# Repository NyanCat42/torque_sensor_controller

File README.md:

# Torque Sensor Controller for VESC E-Bike Assist

This repository contains hardware and firmware for an ESP32-S3 based torque sensor controller that talks to a [VESC](https://github.com/vedderb/bldc) over CAN bus.

The controller reads bottom bracket torque and cadence, computes an assist current target, and sends motor current commands to the VESC. It also tracks odometer data with FRAM-backed persistence and exposes a local web UI for status, tuning, and OTA firmware updates.

## Features

- Torque and cadence based pedal-assist control loop (10 ms period).
- CAN communication to VESC at 500 kbit/s.
- Odometer and speed tracking with persistent FRAM storage.
- Wi-Fi station mode with fallback access point mode.
- Embedded HTTP console for telemetry, runtime config, and calibration.
- OTA firmware upload endpoint.
- TCP bridge for VESC tool connectivity over Wi-Fi.

## Repository Layout

- `lauryno_torque_controller_hardware/`: KiCad schematic, PCB, and BOM.
- `lauryno_torque_controller_software/`: PlatformIO firmware project.
- `documents/`: reference documents, including [torque sensor datasheet](./documents/S135daff485444e569ac136541eaddd83u.pdf).
- `images/`: board render and finished board photo.

## Hardware

Hardware highlights:

- ESP32-S3 module as main controller.
- CAN transceiver interface to VESC.
- FRAM storage for high-endurance persistent data.
- 2 MOSFET outputs and a buck stage for front/rear LED lighting.

The PCB was designed to fit AISLER simple 2-layer constraints for low-cost fabrication.

Available hardware design artifacts:

- Schematic: [lauryno_torque_controller.kicad_sch](./lauryno_torque_controller_hardware/lauryno_torque_controller.kicad_sch)
- PCB layout: [lauryno_torque_controller.kicad_pcb](./lauryno_torque_controller_hardware/lauryno_torque_controller.kicad_pcb)
- BOM: [lauryno_torque_controller.csv](./lauryno_torque_controller_hardware/lauryno_torque_controller.csv)

## Firmware Architecture

Main runtime modules:

- `PedalAssistManager`: torque/cadence processing and motor current command generation.
- `VescCan`: CAN transport and VESC status/current command handling.
- `OdometerManager`: wheel pulse tracking, speed estimation, and persistence.
- `FramStorage`: I2C FRAM read/write backend.
- `NetworkManager`: station connect with timeout and fallback AP startup.
- `OtaHttpServer`: web UI, REST endpoints, and OTA upload flow.
- `VescTcpBridge`: optional TCP bridge (disabled by default).

Task model:

- Pedal-assist control task on core 1.
- Communication task (HTTP + TCP bridge update loop) on core 0.
- Main loop polls CAN and updates odometer processing.

## Quick Start

First flash has to be done over UART, later ones can be done OTA.

1. Install PlatformIO CLI.
2. Open terminal in `lauryno_torque_controller_software/`.
3. Create a local `platformio.secrets.ini` (this file is git-ignored):

```ini
[env:esp32-s3-devkitc-1]
build_flags =
	-DWIFI_STA_SSID=\"YOUR_WIFI_SSID\"
	-DWIFI_STA_PASSWORD=\"YOUR_WIFI_PASSWORD\"
```

4. Build firmware:

```bash
pio run -e esp32-s3-devkitc-1
```

5. Upload over UART (pads at top left of board):

```bash
pio run -e esp32-s3-devkitc-1 -t upload
```

## First Boot Notes

- Device tries configured Wi-Fi STA first, then falls back to AP mode if connection times out.
- AP SSID format: `TorqueCtrl-Setup-<chipid>`.
- mDNS host: `lauryno-dviratis.local`.
- HTTP console runs on port `80`.
- VESC TCP bridge port: `65102` (can be toggled from API/UI).
- **Run pedal sensor zero calibration** after installation using `POST /api/pedal/calibrate_zero`.

## OTA Update

Firmware can be uploaded from the web UI or directly by HTTP multipart upload:

```bash
curl -F "file=@.pio/build/esp32-s3-devkitc-1/firmware.bin" http://lauryno-dviratis.local/api/update
```

After a successful upload, the controller restarts automatically.

## Configuration Baseline

Hardware pins:

- CAN: TX GPIO 15, RX GPIO 7, 500000 bit/s.
- Odometer hall input: GPIO 9.
- FRAM I2C: SDA GPIO 6, SCL GPIO 5, base address `0x50`.
- Torque ADC input: GPIO 1.
- Cadence input: GPIO 2.

VESC IDs: 

- Local controller `42`, target controller `69` (make sure this matches the CAN ID of your VESC).

See `lauryno_torque_controller_software/include/app_config.h` for the full set of constants and limits.

## Open-Source License

This project is licensed under **CERN Open Hardware Licence Version 2 - Permissive** (`CERN-OHL-P-2.0`).

See the repository [LICENSE](./LICENSE) file for the project license notice and the official CERN-OHL-P v2 text reference.

## References

- VESC firmware project: [https://github.com/vedderb/bldc](https://github.com/vedderb/bldc)
- Torque sensor reference document: [S135daff485444e569ac136541eaddd83u.pdf](./documents/S135daff485444e569ac136541eaddd83u.pdf)

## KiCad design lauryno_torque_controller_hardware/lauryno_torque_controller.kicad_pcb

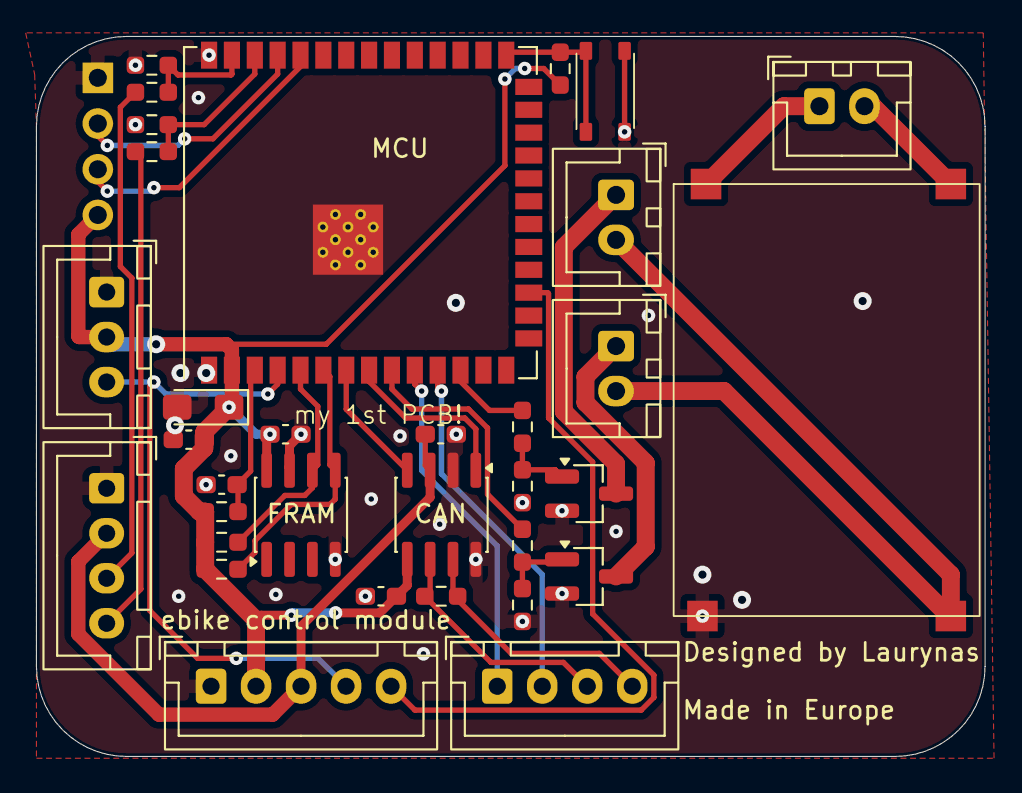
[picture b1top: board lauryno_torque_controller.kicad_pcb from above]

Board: 2 copper layers, 52.7 x 40.0 mm, 34 parts (0 on the bottom side), 27 nets.

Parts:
Battery1: Conn_01x02_Socket; JST_XH_B2B-XH-A_1x02_P2.50mm_Vertical
Boot1: SW_Push; SW_Push_SPST_NO_Alps_SKRK
C2, C4, C5, C6: 0.1u; C_0603_1608Metric_Pad1.08x0.95mm_HandSolder
C3: 1u; C_0603_1608Metric_Pad1.08x0.95mm_HandSolder
C7: 22u; CP_EIA-3216-18_Kemet-A_HandSolder
CAN_chip1: TJA1051T-3; SOIC-8_3.9x4.9mm_P1.27mm
Chineesium_60V_to_12V1: Conn_01x04_Pin; PinHeader_1x04_P2.54mm_Vertical
ESP32: ESP32-S3-WROOM-1; ESP32-S3-WROOM-1U
FRAM1: FM24CL16B; SOIC-8_3.9x4.9mm_P1.27mm
Flashing_UART1: Conn_01x04_Socket; PinHeader_1x04_P2.54mm_Vertical
LED1, LED2: Conn_01x02_Socket; JST_XH_B2B-XH-A_1x02_P2.50mm_Vertical
Q1, Q2: IRLML2502TRPBF; SOT-23_Handsoldering
R1, R4, R7, R8, R9, R12: 10k; R_0603_1608Metric_Pad0.98x0.95mm_HandSolder
R2: 120; R_0603_1608Metric_Pad0.98x0.95mm_HandSolder
R5, R6: 220; R_0603_1608Metric_Pad0.98x0.95mm_HandSolder
R10, R11: 15k; R_0603_1608Metric_Pad0.98x0.95mm_HandSolder
R13, R14: 4.7k; R_0603_1608Metric_Pad0.98x0.95mm_HandSolder
Throttle1: Conn_01x03_Socket; JST_XH_B3B-XH-A_1x03_P2.50mm_Vertical
Torque_sensor1: Conn_01x04_Socket; JST_XH_B4B-XH-A_1x04_P2.50mm_Vertical
VESC1: Conn_01x05_Socket; JST_XH_B5B-XH-A_1x05_P2.50mm_Vertical
VESC_coms1: Conn_01x04_Socket; JST_XH_B4B-XH-A_1x04_P2.50mm_Vertical

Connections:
/3V3: C2.1, C4.1, C6.1, C7.1, CAN_chip1.5 (VIO), ESP32.2 (3V3), FRAM1.8 (VDD), Flashing_UART1.4, R1.1, R4.1, R13.1, R14.1, Throttle1.2, VESC1.2
/5V: C5.1, CAN_chip1.3 (VCC), Torque_sensor1.2, VESC1.3
/CAN_RX: CAN_chip1.1 (TXD), ESP32.8 (IO15)
/CAN_TX: CAN_chip1.4 (RXD), ESP32.7 (IO7)
/LED1_ctrl: ESP32.12 (IO8), R5.1
/LED2_ctrl: ESP32.9 (IO16), R6.1
/LED2_negative: LED2.1, Q2.3 (D)
/Speed: ESP32.38 (IO2), R9.2, R10.1
/Tacho: ESP32.17 (IO9), VESC1.5
/Throttle: ESP32.4 (IO4), Throttle1.3, VESC1.4
/Torque: ESP32.39 (IO1), R11.1, R12.2
/U1RXD: ESP32.11 (IO18), VESC_coms1.2
/U1TXD: ESP32.10 (IO17), VESC_coms1.1
/VLED: Chineesium_60V_to_12V1.2, LED2.2
GND: Boot1.1, C2.2, C3.1, C4.2, C5.2, C6.2, C7.2, CAN_chip1.2 (GND), CAN_chip1.8 (S), Chineesium_60V_to_12V1.3, ESP32.1 (GND), ESP32.40 (GND), ESP32.41 (GND), FRAM1.4 (VSS), FRAM1.7 (WP), Flashing_UART1.1, Q1.2 (S), Q2.2 (S), R7.1, R8.1, R10.2, R11.2, Throttle1.1, Torque_sensor1.1, VESC1.1
unnamed: CAN_chip1.7 (CANH), R2.1, VESC_coms1.4
unnamed: CAN_chip1.6 (CANL), R2.2, VESC_coms1.3
unnamed: C3.2, ESP32.3 (EN), R1.2
unnamed: Boot1.2, ESP32.27 (IO0), R4.2
unnamed: ESP32.5 (IO5), FRAM1.6 (SCL), R14.2
unnamed: ESP32.6 (IO6), FRAM1.5 (SDA), R13.2
unnamed: ESP32.36 (RXD0), Flashing_UART1.3
unnamed: ESP32.37 (TXD0), Flashing_UART1.2
unnamed: Q1.1 (G), R5.2, R7.2
unnamed: Q2.1 (G), R6.2, R8.2
unnamed: R12.1, Torque_sensor1.3
unnamed: R9.1, Torque_sensor1.4

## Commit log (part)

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2026-04-26 initial firmware for final hardware
2026-04-26 update readme and license
2026-04-26 update photo
